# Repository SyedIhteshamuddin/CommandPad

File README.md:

# CommandPad
---
A 5-key macropad with rotary encoder, and rgb LEDs. Which is used for all ur imp shortcuts!

Note: This ReadME is writtern by Syed Ihteshamuddin (human ofc), So if some mistakes are occurred please highlight.   

## Overview 
---
This is my first complete hardware project, I have spent over 20+ hours on this project.

---

## Project Gallery

### SCHEMATIC

I have used global tags in my schematic to make it clean and clear, But Assigning footprints and finding relevant 3d models for the components for me was a very difficult task :) 

---

### PCB LAYOUT

I have manually routed the PCB , it was somewhat challenging to overcome the *Board Clearance* issues. The PCB has 0 errors (DRC) except silkscreen warnings. 

---

### CAD Designing 

I was CAD designing FIRST TIME. So, it was not easy for me. I have designed this case in Autodesk Fusion. This design is a "SANDWITCH STYLE MACROPAD" where it consists of two plates; Top plate, Bottom Case and PCB gets sandwiched between them. They are all screwed up with M3 Screws. All the design was done in +0.04 tolerance for better results!

#### Assembly View

#### Top Plate

#### Bottom Plate

---

## BOM - Bill of Materials

| # | Component | Qty | Source |
|---:|---|---:|---|
| 1 | Seeed Studio XIAO RP2040 | 1 | Hack Club Kit |
| 2 | Gateron KS-3 MX Switches | 5 | Hack Club Kit |
| 3 | 1N4148 Through-hole Diodes | 5 | Hack Club Kit |
| 4 | Alps EC11E Rotary Encoder | 1 | Hack Club Kit |
| 5 | SK6812 MINI-E RGB LEDs | 5 | Hack Club Kit |
| 6 | 0.91-inch SSD1306 OLED Display (128×32) | 1 | Hack Club Kit |
| 7 | White DSA Keycaps | 5 | Hack Club Kit |
| 8 | M3×16 mm Screws (trim to 13 mm) | 4 | Hack Club Kit |
| 9 | M3×5 mm × 4 mm Heat-set Inserts | 4 | Hack Club Kit |
| 10 | 3D-Printed Case (Base + Top Plate) | 1 set | Self-fabricated |

## Notes

- **Controller:** Seeed Studio XIAO RP2040.
- **Input:** 5 MX-style mechanical switches and one rotary encoder with push switch.
- **Display:** 0.91-inch SSD1306 OLED, 128×32 resolution.
- **Lighting:** 5 SK6812 MINI-E addressable RGB LEDs.
- **Enclosure:** 3D-printed base and top plate.

---

## Function

| Key / Component | Shortcut / Input | Function |
|---|---|---|
| Key 1 (SW1) | `Ctrl + C` | Copies selected text, files, or items |
| Key 2 (SW2) | `Ctrl + V` | Pastes copied content |
| Key 3 (SW3) | `Ctrl + Z` | Undoes the last action in supported applications |
| Key 4 (SW4) | `Alt + Tab` | Switches between open windows |
| Key 5 (SW5) | `Win + Shift + S` | Opens the Windows screenshot/snipping interface |
| Rotary Encoder (Clockwise) | Volume Up | Increases system volume |
| Rotary Encoder (Counterclockwise) | Volume Down | Decreases system volume |
| Rotary Encoder (Press) | Mute Toggle | Toggles system mute |
| OLED Display | I²C | Displays a greeting and action/status messages |
| 5 × RGB LEDs | Addressable LED control | Provides visual feedback when keys are pressed |
| XIAO RP2040 | CircuitPython + USB HID | Processes inputs and sends keyboard/media commands |

> **status:** The displayed volume percentage is an estimate, not the computer's actual volume reading.

---
## AI Usage

I used AI to gather resources for footprints and 3d models, and also for Firmware. Rest all work is done by me! [ For Proof : You can check Lapse recording ] 

---

## Credits

- **HackClub:** - for organizing the program
- **CircuitPython:** - Python Firmware
- **Hackpad Team:** - for tutorials and resources
- Special thanks to "https://github.com/damnitzhemanth-oss" (hemanth) for personally helping me build this project!

---

## License

OPEN SOURCE, enjoy :) 

( I aint responsible if it turns out to be a time bomb).

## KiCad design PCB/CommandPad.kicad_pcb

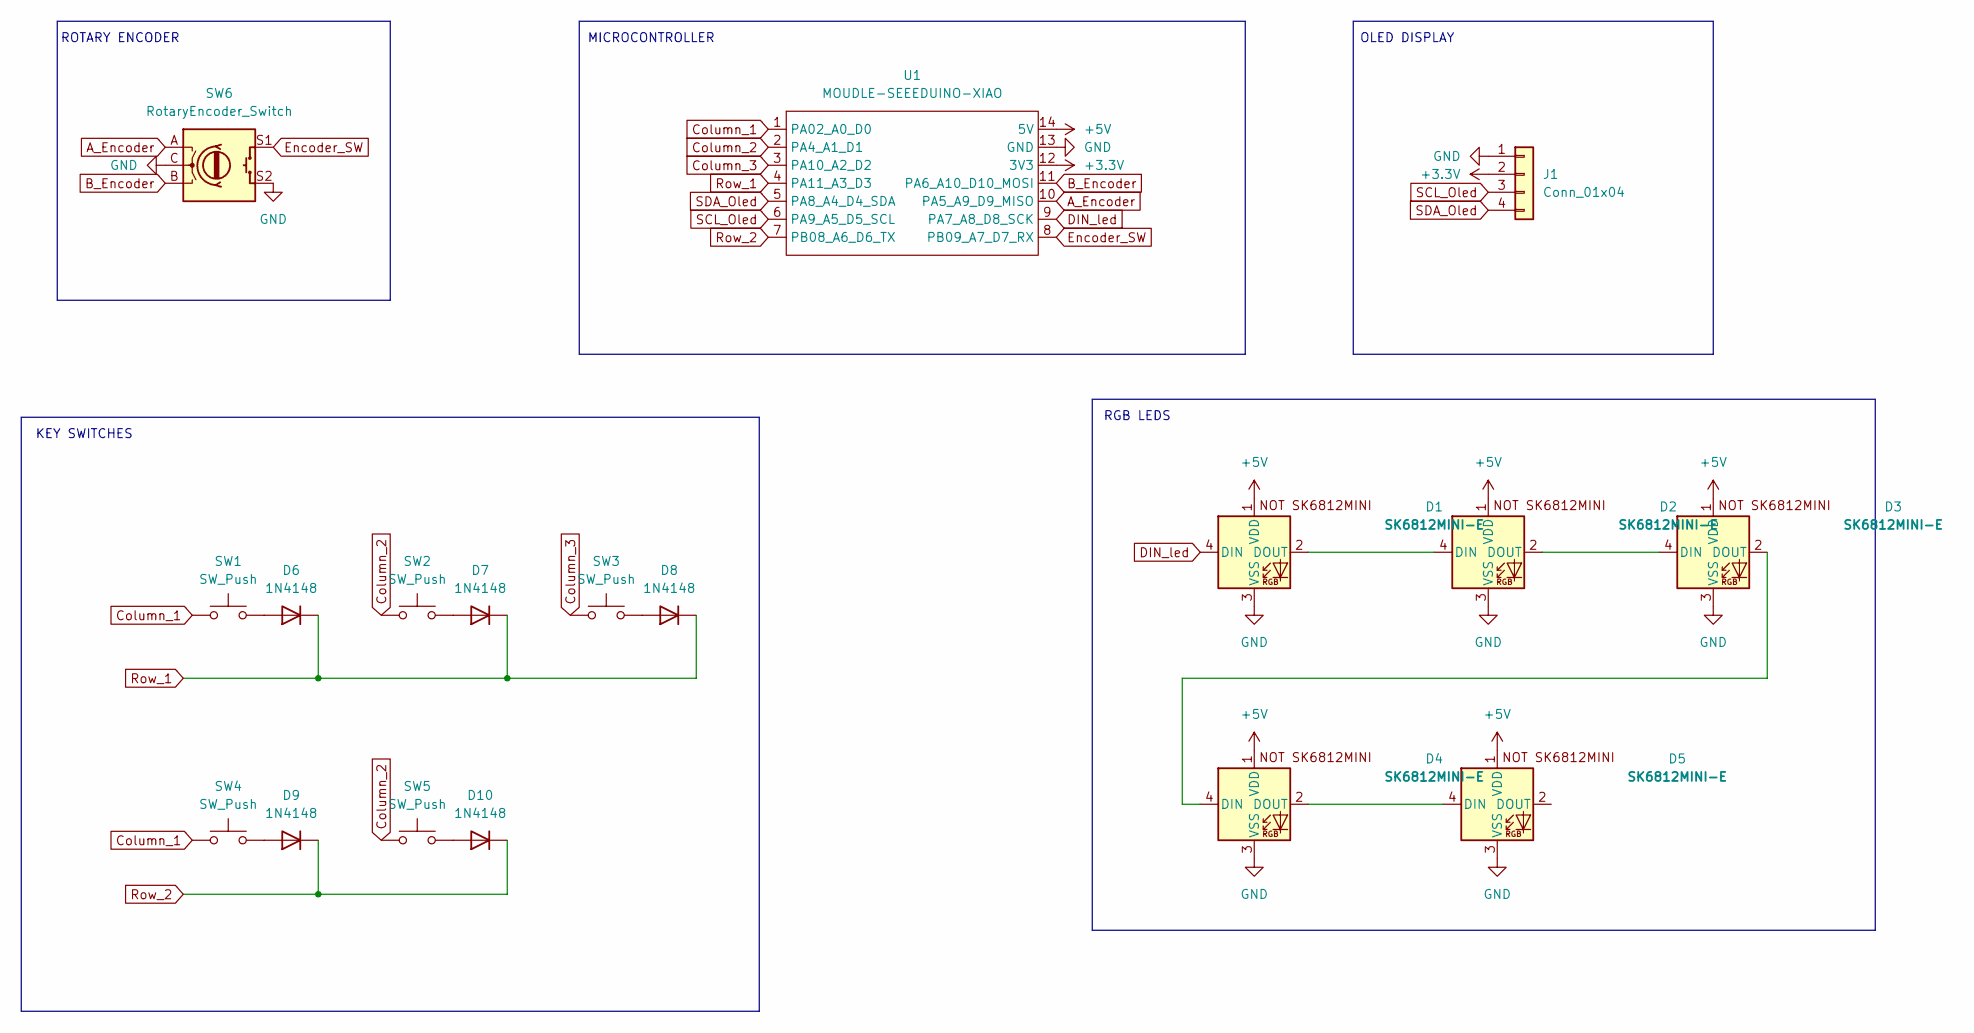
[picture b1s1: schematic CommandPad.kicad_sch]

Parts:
D1, D2, D3, D4, D5: SK6812MINI-E; SK6812MINI-E (sml pads)
D6, D7, D8, D9, D10: 1N4148; D_DO-35_SOD27_P7.62mm_Horizontal
J1: Conn_01x04; FanPinHeader_1x04_P2.54mm_Vertical
SW1, SW2, SW3, SW4, SW5: SW_Push; SW_Cherry_MX_1.00u_PCB
SW6: RotaryEncoder_Switch; RotaryEncoder_Alps_EC11E-Switch_Vertical_H20mm
U1: MOUDLE-SEEEDUINO-XIAO; XIAO-Generic-Hybrid-14P-2.54-21X17.8MM

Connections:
+3.3V: J1.2 (VCC), U1.12 (3V3)
+5V: D1.1 (VDD), D2.1 (VDD), D3.1 (VDD), D4.1 (VDD), D5.1 (VDD), U1.14 (5V)
A_Encoder: SW6.A, U1.10 (PA5_A9_D9_MISO)
B_Encoder: SW6.B, U1.11 (PA6_A10_D10_MOSI)
Column_1: SW1.1, SW4.1, U1.1 (PA02_A0_D0)
Column_2: SW2.1, SW5.1, U1.2 (PA4_A1_D1)
Column_3: SW3.1, U1.3 (PA10_A2_D2)
DIN_led: D1.4 (DIN), U1.9 (PA7_A8_D8_SCK)
Encoder_SW: SW6.S1, U1.8 (PB09_A7_D7_RX)
GND: D1.3 (VSS), D2.3 (VSS), D3.3 (VSS), D4.3 (VSS), D5.3 (VSS), J1.1 (GND), SW6.C, SW6.S2, U1.13 (GND)
unnamed: D1.2 (DOUT), D2.4 (DIN)
unnamed: D2.2 (DOUT), D3.4 (DIN)
unnamed: D3.2 (DOUT), D4.4 (DIN)
unnamed: D4.2 (DOUT), D5.4 (DIN)
unnamed: D6.2 (A), SW1.2
unnamed: D7.2 (A), SW2.2
unnamed: D8.2 (A), SW3.2
unnamed: D9.2 (A), SW4.2
unnamed: D10.2 (A), SW5.2
Row_1: D6.1 (K), D7.1 (K), D8.1 (K), U1.4 (PA11_A3_D3)
Row_2: D9.1 (K), D10.1 (K), U1.7 (PB08_A6_D6_TX)
SCL_Oled: J1.3 (SCL), U1.6 (PA9_A5_D5_SCL)
SDA_Oled: J1.4 (SDA), U1.5 (PA8_A4_D4_SDA)

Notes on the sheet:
ROTARY ENCODER
RGB LEDS
OLED DISPLAY
MICROCONTROLLER
KEY SWITCHES

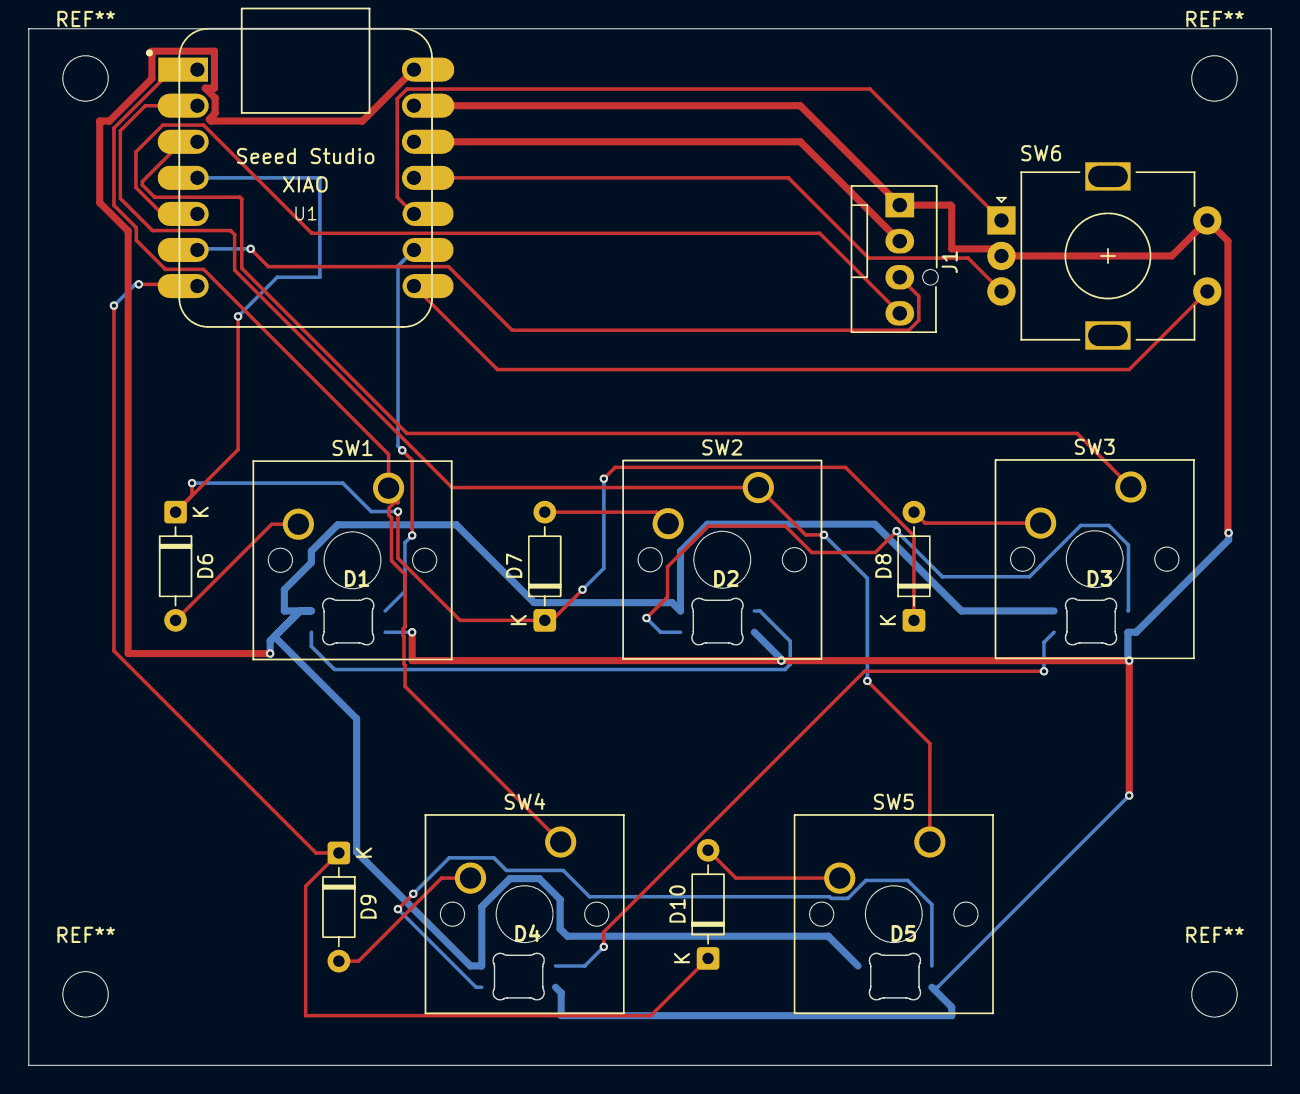
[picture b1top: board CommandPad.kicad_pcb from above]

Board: 2 copper layers, 87.5 x 73.0 mm, 18 parts (0 on the bottom side), 23 nets.
